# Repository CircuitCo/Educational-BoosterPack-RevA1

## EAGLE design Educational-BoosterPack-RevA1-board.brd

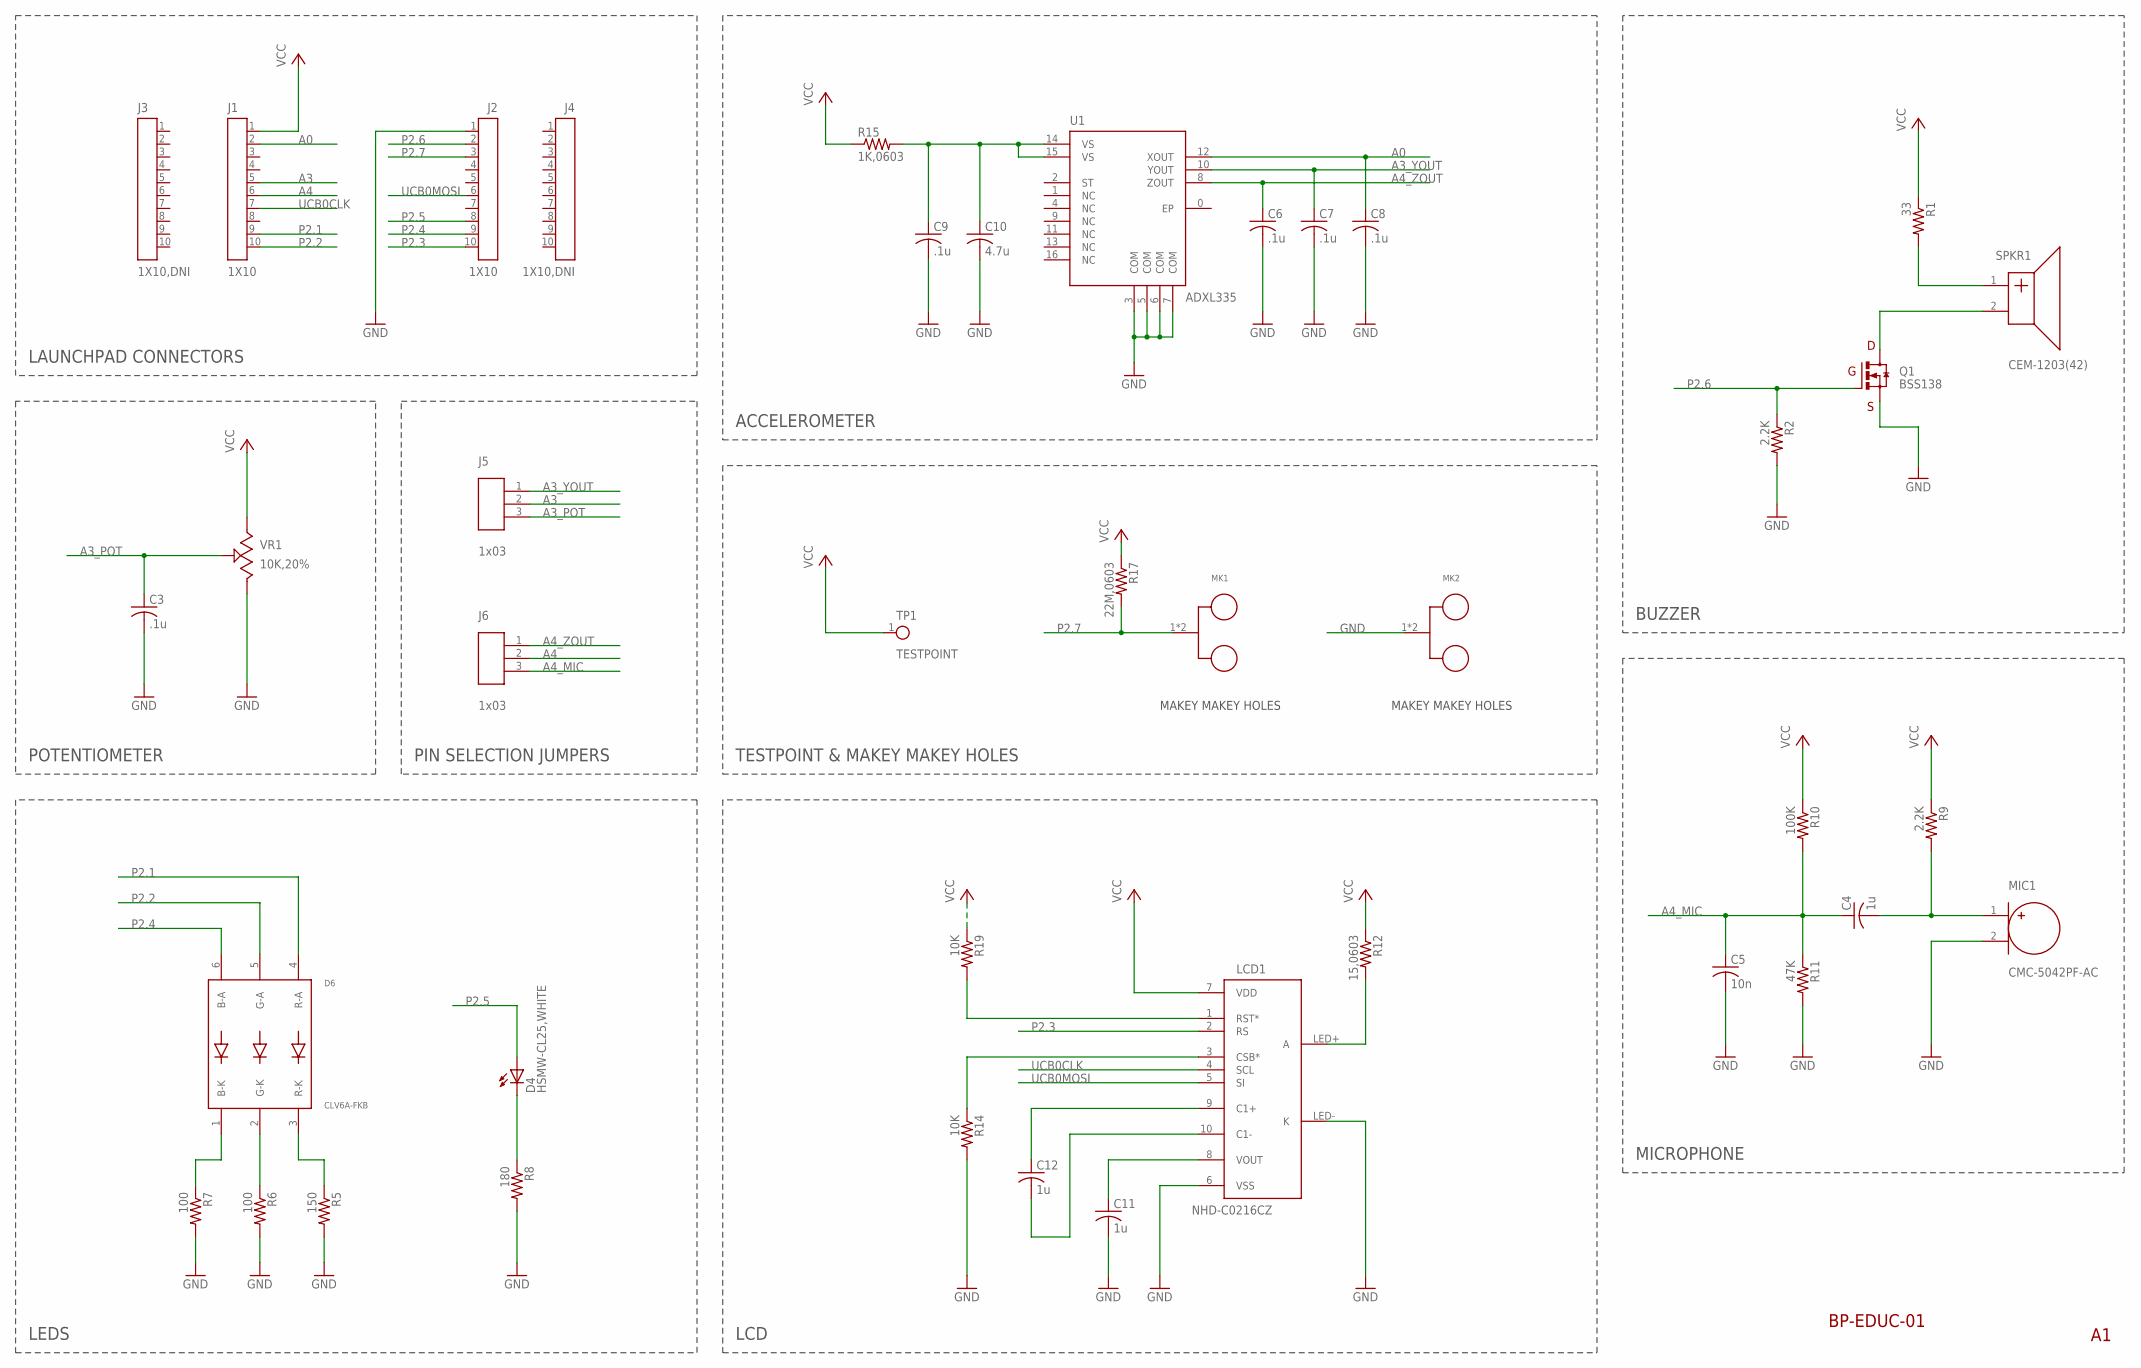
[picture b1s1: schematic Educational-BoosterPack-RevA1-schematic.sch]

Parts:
C3, C6, C7, C8, C9: .1u; C0402
C4, C11, C12: 1u; C0402
C5: 10n; C0402
C10: 4.7u; C0603
D4: HSMW-CL25,WHITE; CHIPLED_0603
D6: CLV6A-FKB; TRICOLOR-LED6
J1, J2: 1X10
J3, J4: 1X10,DNI; 1X10
J5, J6: 1x03; 1X03
LCD1: NHD-C0216CZ; GENERIC-LCD10-2
MIC1: CMC-5042PF-AC; GENERIC-2PADS2
MK1, MK2: MAKEYMAKEY
Q1: BSS138; SOT23-3
R1: 33; R0402
R2, R9: 2.2K; R0402
R5: 150; R0402
R6, R7: 100; R0402
R8: 180; R0402
R10: 100K; R0402
R11: 47K; R0402
R12: 15,0603; R0603
R14, R19: 10K; R0402
R15: 1K,0603; R0603
R17: 22M,0603; R0603
SPKR1: CEM-1203(42); GENERIC-2PADS
TP1: TESTPOINT
U1: ADXL335; LFCSP-16
VR1: 10K,20%; GENERIC-3HOLES

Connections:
A0: C8.1, J1.2, U1.12 (XOUT)
A3: J1.5, J5.2
A3_POT: C3.1, J5.3, VR1.2
A3_YOUT: C7.1, J5.1, U1.10 (YOUT)
A4: J1.6, J6.2
A4_MIC: C4.1, C5.1, J6.3, R10.2, R11.1
A4_ZOUT: C6.1, J6.1, U1.8 (ZOUT)
GND: C3.2, C5.2, C6.2, C7.2, C8.2, C9.2, C10.2, C11.2, J2.1, LCD1.6 (VSS), LCD1.LED- (K), MIC1.2 (MIC_N), MK2.1, MK2.2, Q1.2 (S), R2.2, R5.2, R6.2, R7.2, R8.2, R11.2, R14.2, U1.3 (COM), U1.5 (COM), U1.6 (COM), U1.7 (COM), VR1.3
unnamed: C9.1, C10.1, R15.2, U1.14 (VS), U1.15 (VS)
unnamed: C4.2, MIC1.1 (MIC_P), R9.2
unnamed: LCD1.LED+ (A), R12.2
unnamed: D6.2 (G-K), R6.1
unnamed: R1.2, SPKR1.1 (SPKR_P)
unnamed: Q1.3 (D), SPKR1.2 (SPKR_N)
unnamed: LCD1.3 (CSB*), R14.1
unnamed: D6.3 (R-K), R5.1
unnamed: D6.1 (B-K), R7.1
unnamed: C11.1, LCD1.8 (VOUT)
unnamed: C12.2, LCD1.10 (C1-)
unnamed: C12.1, LCD1.9 (C1+)
unnamed: LCD1.1 (RST*), R19.2
unnamed: D4.C, R8.1
P2.1: D6.4 (R-A), J1.9
P2.2: D6.5 (G-A), J1.10
P2.3: J2.10, LCD1.2 (RS)
P2.4: D6.6 (B-A), J2.9
P2.5: D4.A, J2.8
P2.6: J2.2, Q1.1 (G), R2.1
P2.7: J2.3, MK1.1, MK1.2, R17.2
UCB0CLK: J1.7, LCD1.4 (SCL)
UCB0MOSI: J2.6, LCD1.5 (SI)
VCC: J1.1, LCD1.7 (VDD), R1.1, R9.1, R10.1, R12.1, R15.1, R17.1, R19.1, TP1.1, VR1.1

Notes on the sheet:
MAKEY MAKEY HOLES
LAUNCHPAD CONNECTORS
POTENTIOMETER
ACCELEROMETER
BUZZER
MICROPHONE
LCD
LEDS
TESTPOINT & MAKEY MAKEY HOLES
PIN SELECTION JUMPERS
BP-EDUC-01

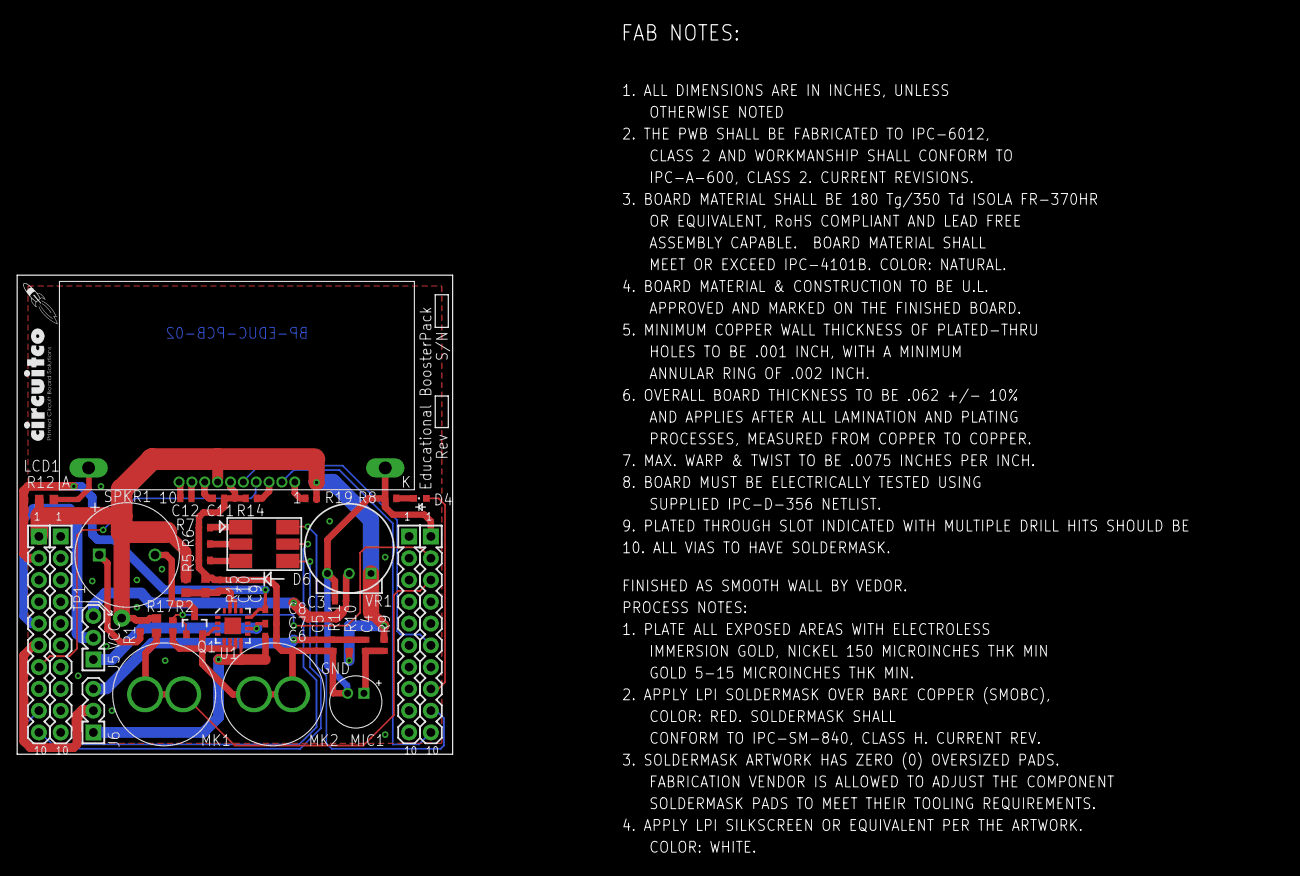
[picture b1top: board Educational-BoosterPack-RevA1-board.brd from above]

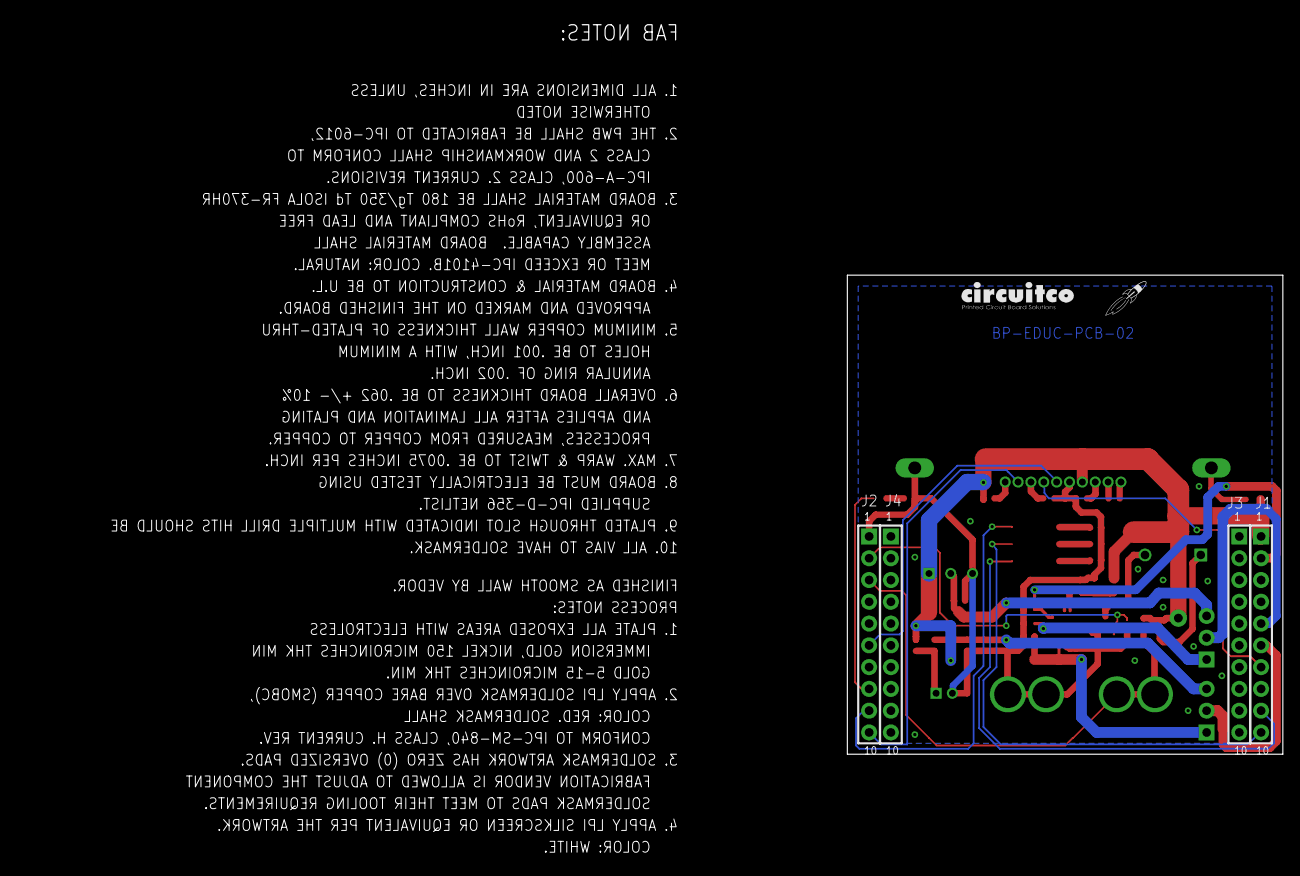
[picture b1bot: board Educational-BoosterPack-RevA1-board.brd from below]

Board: 2 copper layers, 147.6 x 98.2 mm, 45 parts (2 on the bottom side), 32 nets.

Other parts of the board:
E$1, E$3: LOGO-CIRCUITCO
E$2, E$4: LOGO-ROCKET

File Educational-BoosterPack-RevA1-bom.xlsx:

EDUCATIONAL BOOSTERPACK |  |  |  | Revised: | 41246
BP-EDUC-01 Revision: A1
ITM | QTY | REF DESIGNATOR | PART | PCB FOOTPRINT | DESCRIPTION | MANU | MANU P/N | VENDOR | VENFOR P/N
1 | 5 | C3,C6,C7,C8,C9 | 0.1uF | 402 | CAP CER 0.1UF 10V 10% X5R 0402 | TAIYO | LMK105BJ104KV-F | DK | 587-1227-1-ND
2 | 3 | C4,C11,C12 | 1uF | 402 | CAP CER 1UF 6.3V 10% X5R 0402 | TAIYO | JMK105BJ105KV-F | DK | 587-1231-1-ND
3 | 1 | C5 | 10nF | 402 | CAP CER 10000PF 16V 10% X7R 0402 | YAGEO | CC0402KRX7R7BB103 | DK | 311-1042-1-ND
4 | 1 | C10 | 4.7uF | 603 | CAP CER 4.7UF 6.3V 20% X5R 0603 | MURATA | GRM188R60J475ME19D | DK | 490-5421-1-ND
5 | 1 | D4 | SMW-CL25 | LED603 | LED CHIPLED INGAN WHT TOP SMD | AVAGO | HSMW-CL25 | DK | 516-2278-1-ND
6 | 1 | D6 | CLV6A-FKB | TRICOLOR | LED RED/GREEN/BLUE PLCC6 SMD | CREE | CLV6A-FKB-CK1P1G1BB7R3R3 | DK | CLV6A-FKB-CK1P1G1BB7R3R3CT-ND
7 | 2 | J1,J2 | 1X10 | HEADER1X10 | CONN HEADER FMALE 10POS .1" GOLD | SULLINS | PPPC101LFBN-RC | DK | S7043-ND
8 | 0 | J3,J4 | 1X10,DNI | HEADER1X10 | CONN HEADER FMALE 10POS .1" GOLD | SULLINS | PPPC101LFBN-RC | DK | S7043-ND
9 | 2 | J5,J6 | 1X03 | HEADER1X03 | CONN HEADER .100 SINGL STR 3POS | SULLINS | PEC03SAAN | DK | S1012E-03-ND
10 | 1 | LCD1 | NHD-C0216CZ | LCD | LCD COG CHAR 2X16 WHT TRANSFL | NEWHAVEN | NHD-C0216CZ-FSW-FBW-3V3 | DK | NHD-C0216CZ-FSW-FBW-3V3-ND
11 | 1 | MIC1 | CMC-5042PF-AC | MIC | MIC COND ANALOG OMNI -42DB | CUI | CMC-5042PF-AC | DK | 102-1724-ND
12 | 2 | MK1,MK2 | MAKEYMAKEY | MAKEYMAKEY | MAKEY MAKEY HOLES | N/A | N/A | N/A | N/A
13 | 1 | Q1 | BSS138 | SOT23-3 | MOSFET N-CH 50V 200MA SOT23-3 | DIODES | BSS138-7-F | DK | BSS138-FDICT-ND
14 | 1 | R1 | 33 | 402 | RES 33 OHM 1/16W 5% 0402 SMD | YAGEO | RC0402JR-0733RL | DK | 311-33JRCT-ND
15 | 2 | R2,R9 | 2.2K | 402 | RES 2.2K OHM 1/16W 5% 0402 SMD | VISHAY | CRCW04022K20JNED | DK | 541-2.2KJCT-ND
16 | 1 | R5 | 150 | 402 | RES 150 OHM 1/16W 5% 0402 SMD | YAGEO | RC0402JR-07150RL | DK | 311-150JRCT-ND
17 | 2 | R6,R7 | 100 | 402 | RES 100 OHM 1/16W 5% 0402 SMD | YAGEO | RC0402JR-07100RL | DK | 311-100JRCT-ND
18 | 1 | R8 | 180R, 5% | 402 | RES 180 OHM 1/16W 5% 0402 SMD | YAGEO | RC0402JR-07180RL | DK | 311-180JRCT-ND
19 | 1 | R10 | 100K | 402 | RES 100K OHM 1/16W 5% 0402 SMD | VISHAY | CRCW0402100KJNED | DK | 541-100KJCT-ND
20 | 1 | R11 | 47K | 402 | RES 47K OHM 1/16W 5% 0402 SMD | VISHAY | CRCW040247K0JNED | DK | 541-47KJCT-ND
21 | 1 | R12 | 15R, 0603 | 603 | RES 15 OHM .25W 5% 0603 SMD | VISHAY | CRCW060315R0JNEAHP | DK | CRCW060315R0JNEAHPCT-ND
22 | 2 | R14,R19 | 10K | 402 | RES 10K OHM 1/16W 5% 0402 SMD | VISHAY | CRCW040210K0JNED | DK | 541-10KJCT-ND
23 | 1 | R15 | 1K,0603 | 603 | RES 1.0K OHM 1/10W 5% 0603 SMD | VISHAY | CRCW06031K00JNEA | DK | 541-1.0KGCT-ND
24 | 1 | R17 | 22M,0603 | 603 | RES 22M OHM 1/10W 10% 0603 SMD | PANASONIC | ERJ-3GEYK226V | DK | P22MGCT-ND
25 | 2 | SH1,SH2 | SHUNT | SHUNT | CONN JUMPER SHORTING GOLD FLASH | SULLINS | SPC02SYAN | DK | S9001-ND
26 | 1 | SPKR1 | BUZZER | BUZZER | BUZZER 2.048KHZ 12MM PC MOUNT | CUI | CEM-1203(42) | DK | 102-1153-ND
27 | 1 | TP1 | TESTPOINT | TP | TESTPOINT HOLE | N/A | N/A | N/A | N/A
28 | 1 | U1 | ADXL335 | 16LFCSP | IC ACCELEROMETER 3AXL 3G 16LFCSP | ANALOG | ADXL335BCPZ-RL7 | DK | ADXL335BCPZ-RL7CT-ND
29 | 1 | VR1 | 10K,20% | POT | POT 10K OHM THUMBWHEEL CERM ST | BOURNS | 3352T-1-103LF | DK | 3352T-103LF-ND
30 | 1 | PCB

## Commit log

2012-12-03 init
2012-12-03 rm brd ger
2012-12-03 add manu
2012-12-03 rm sch
2012-12-03 add sch
2012-12-04 rm MK
2012-12-04 add gator
